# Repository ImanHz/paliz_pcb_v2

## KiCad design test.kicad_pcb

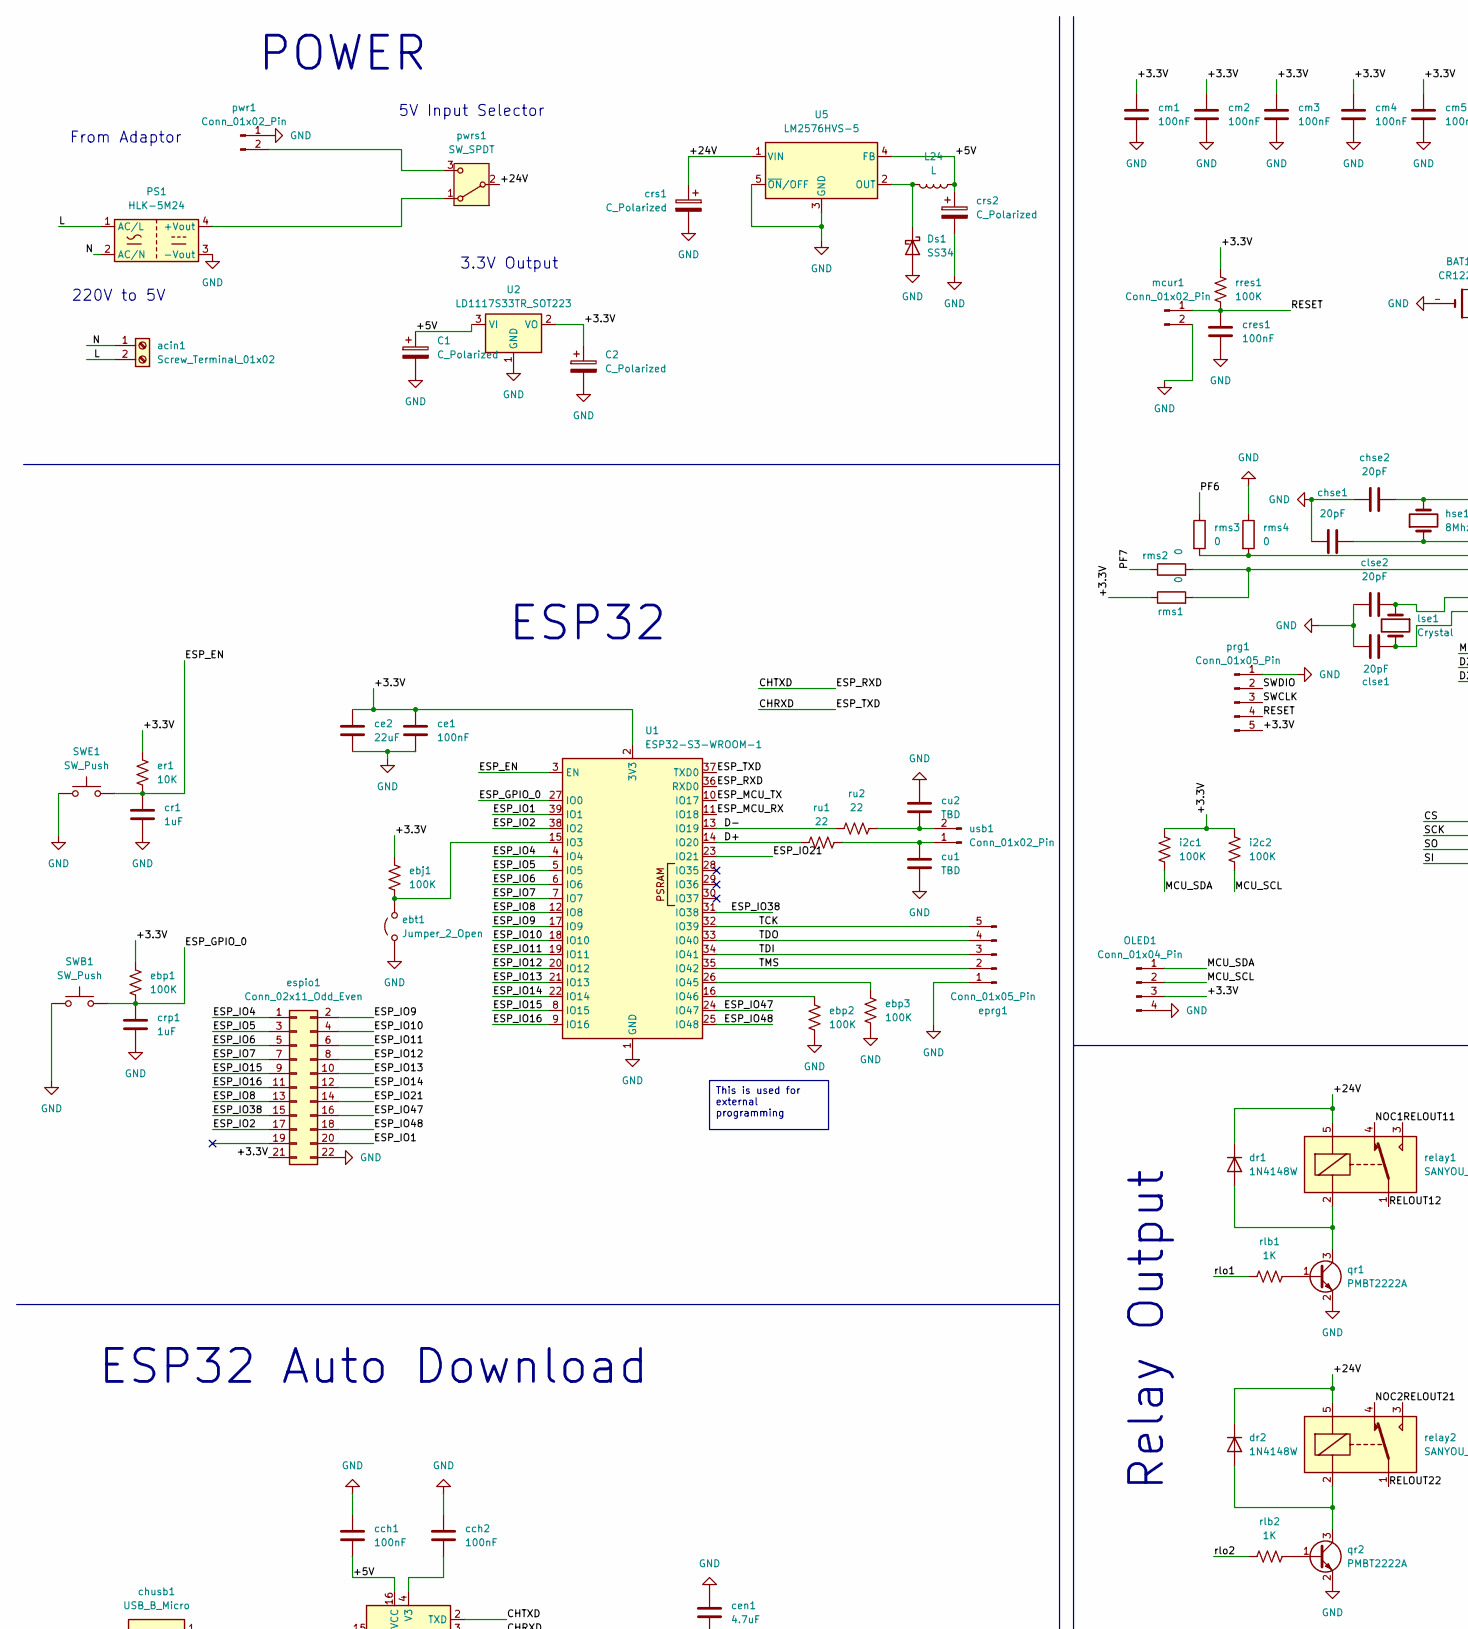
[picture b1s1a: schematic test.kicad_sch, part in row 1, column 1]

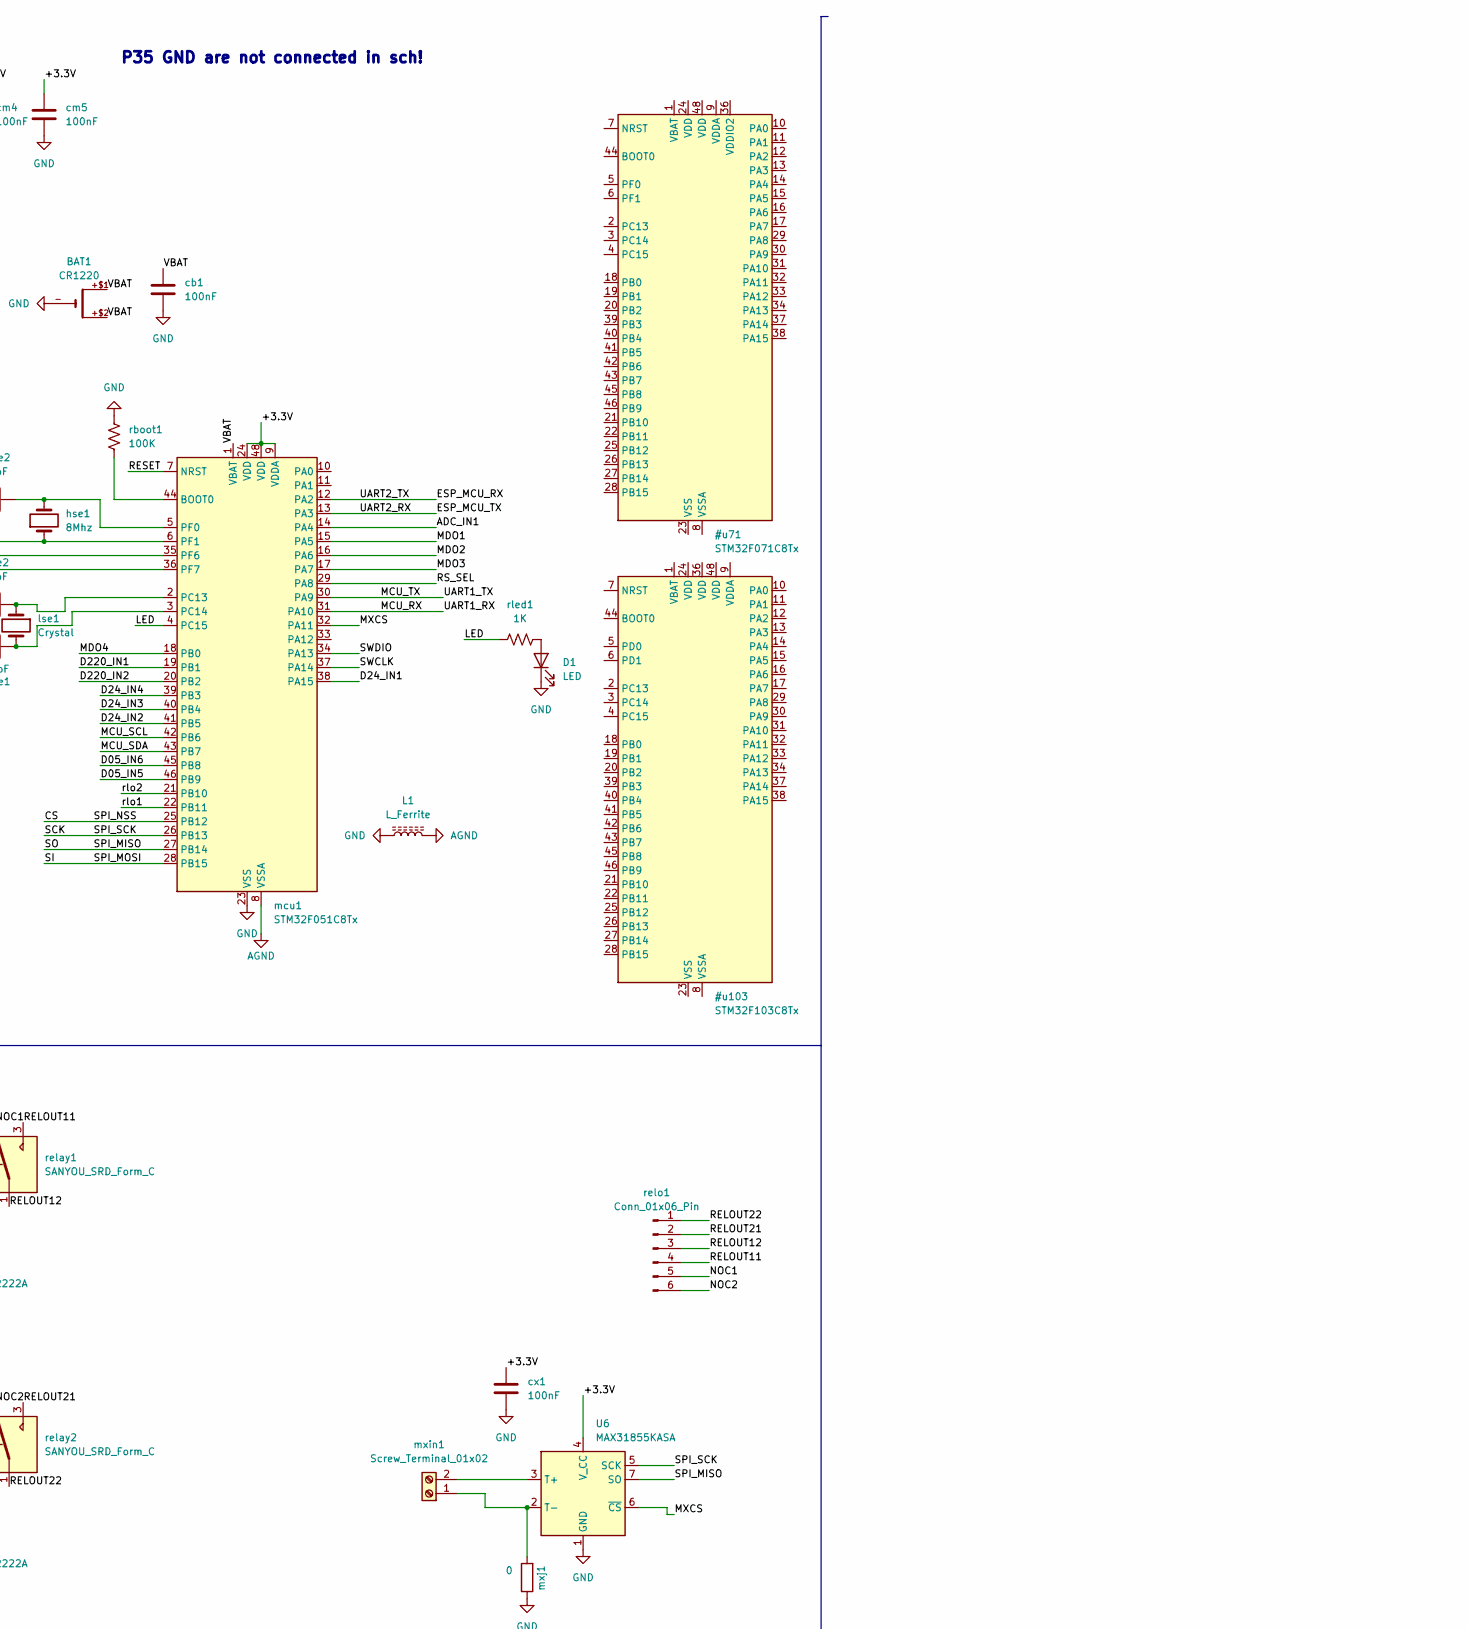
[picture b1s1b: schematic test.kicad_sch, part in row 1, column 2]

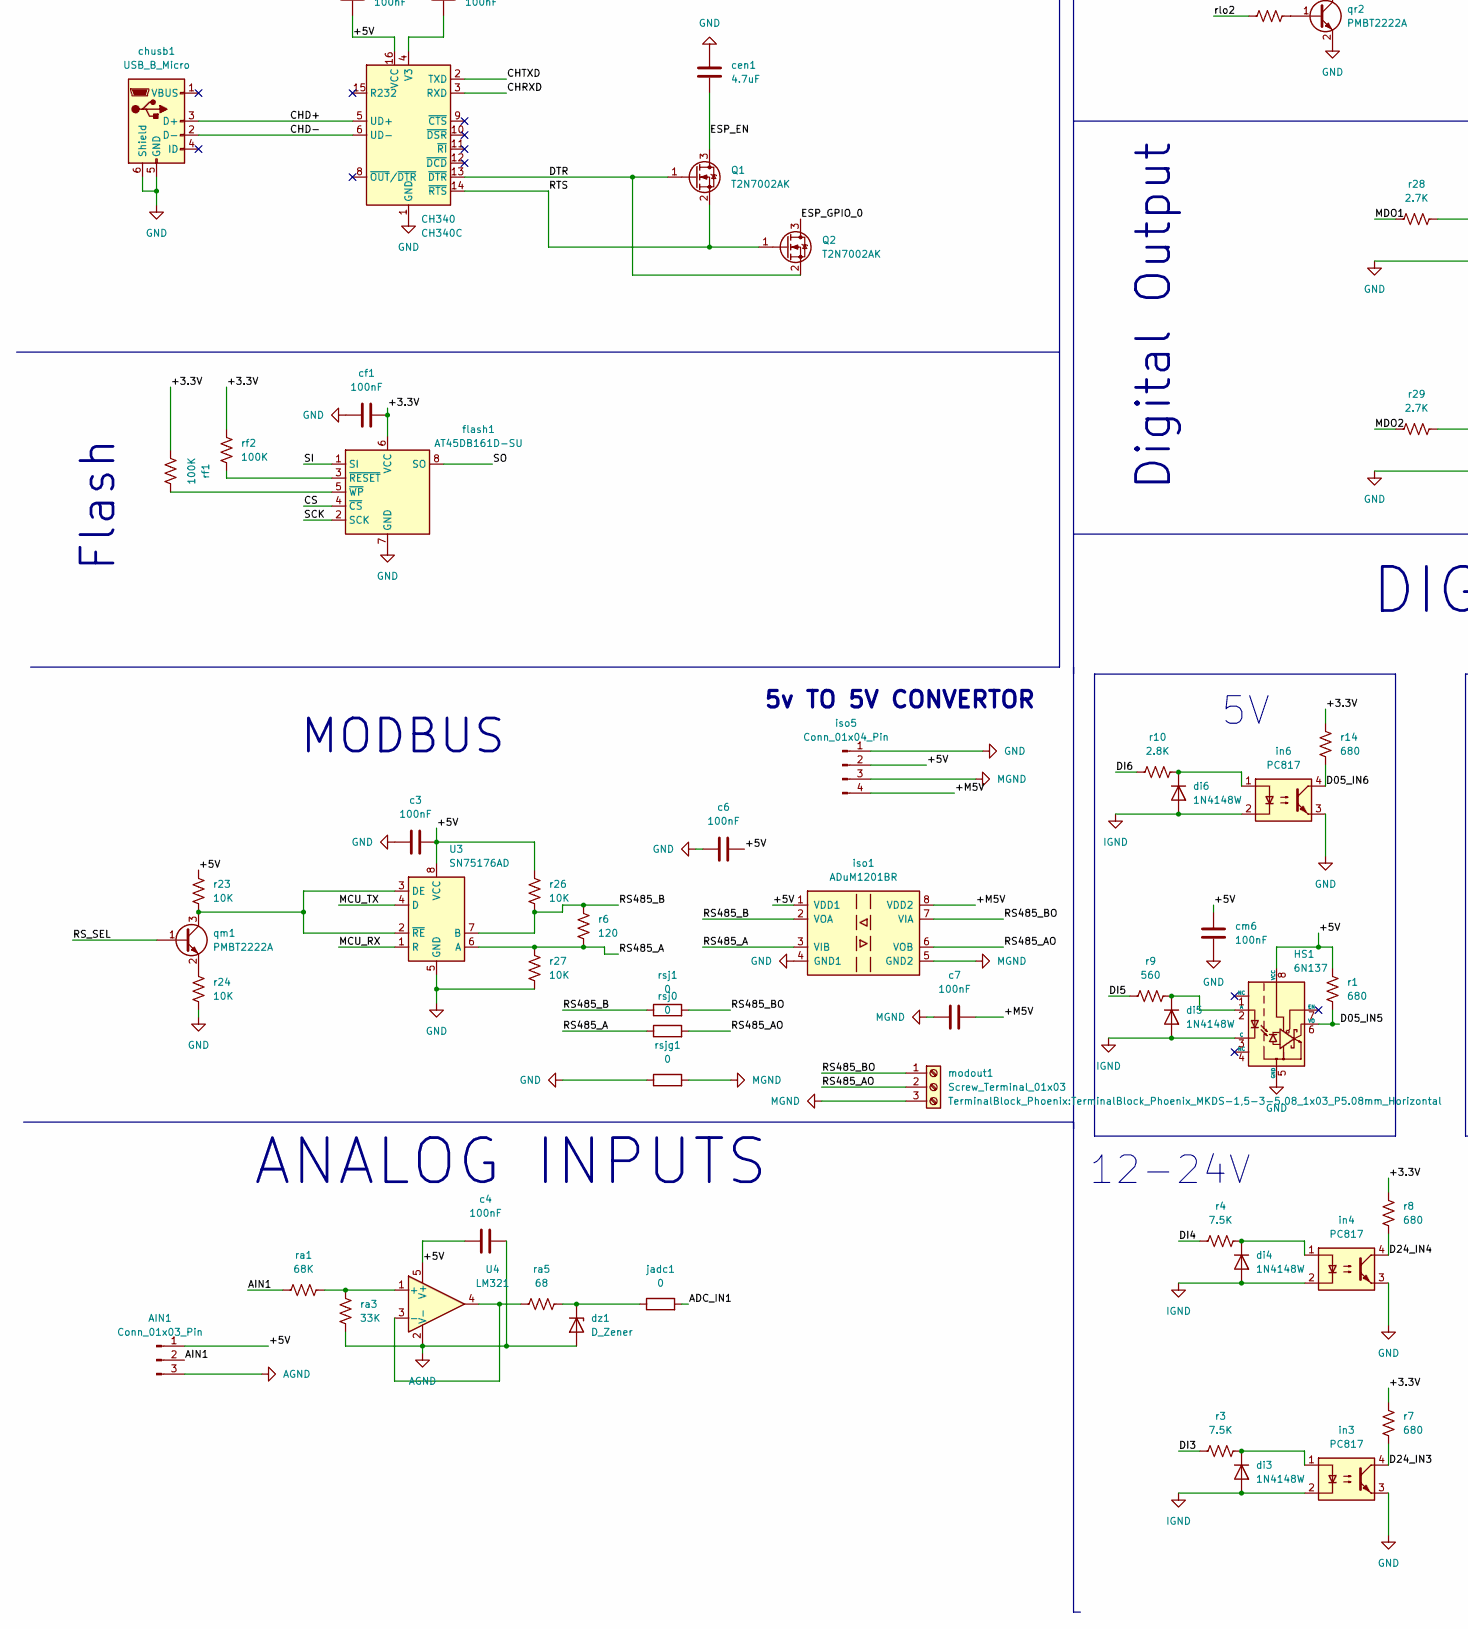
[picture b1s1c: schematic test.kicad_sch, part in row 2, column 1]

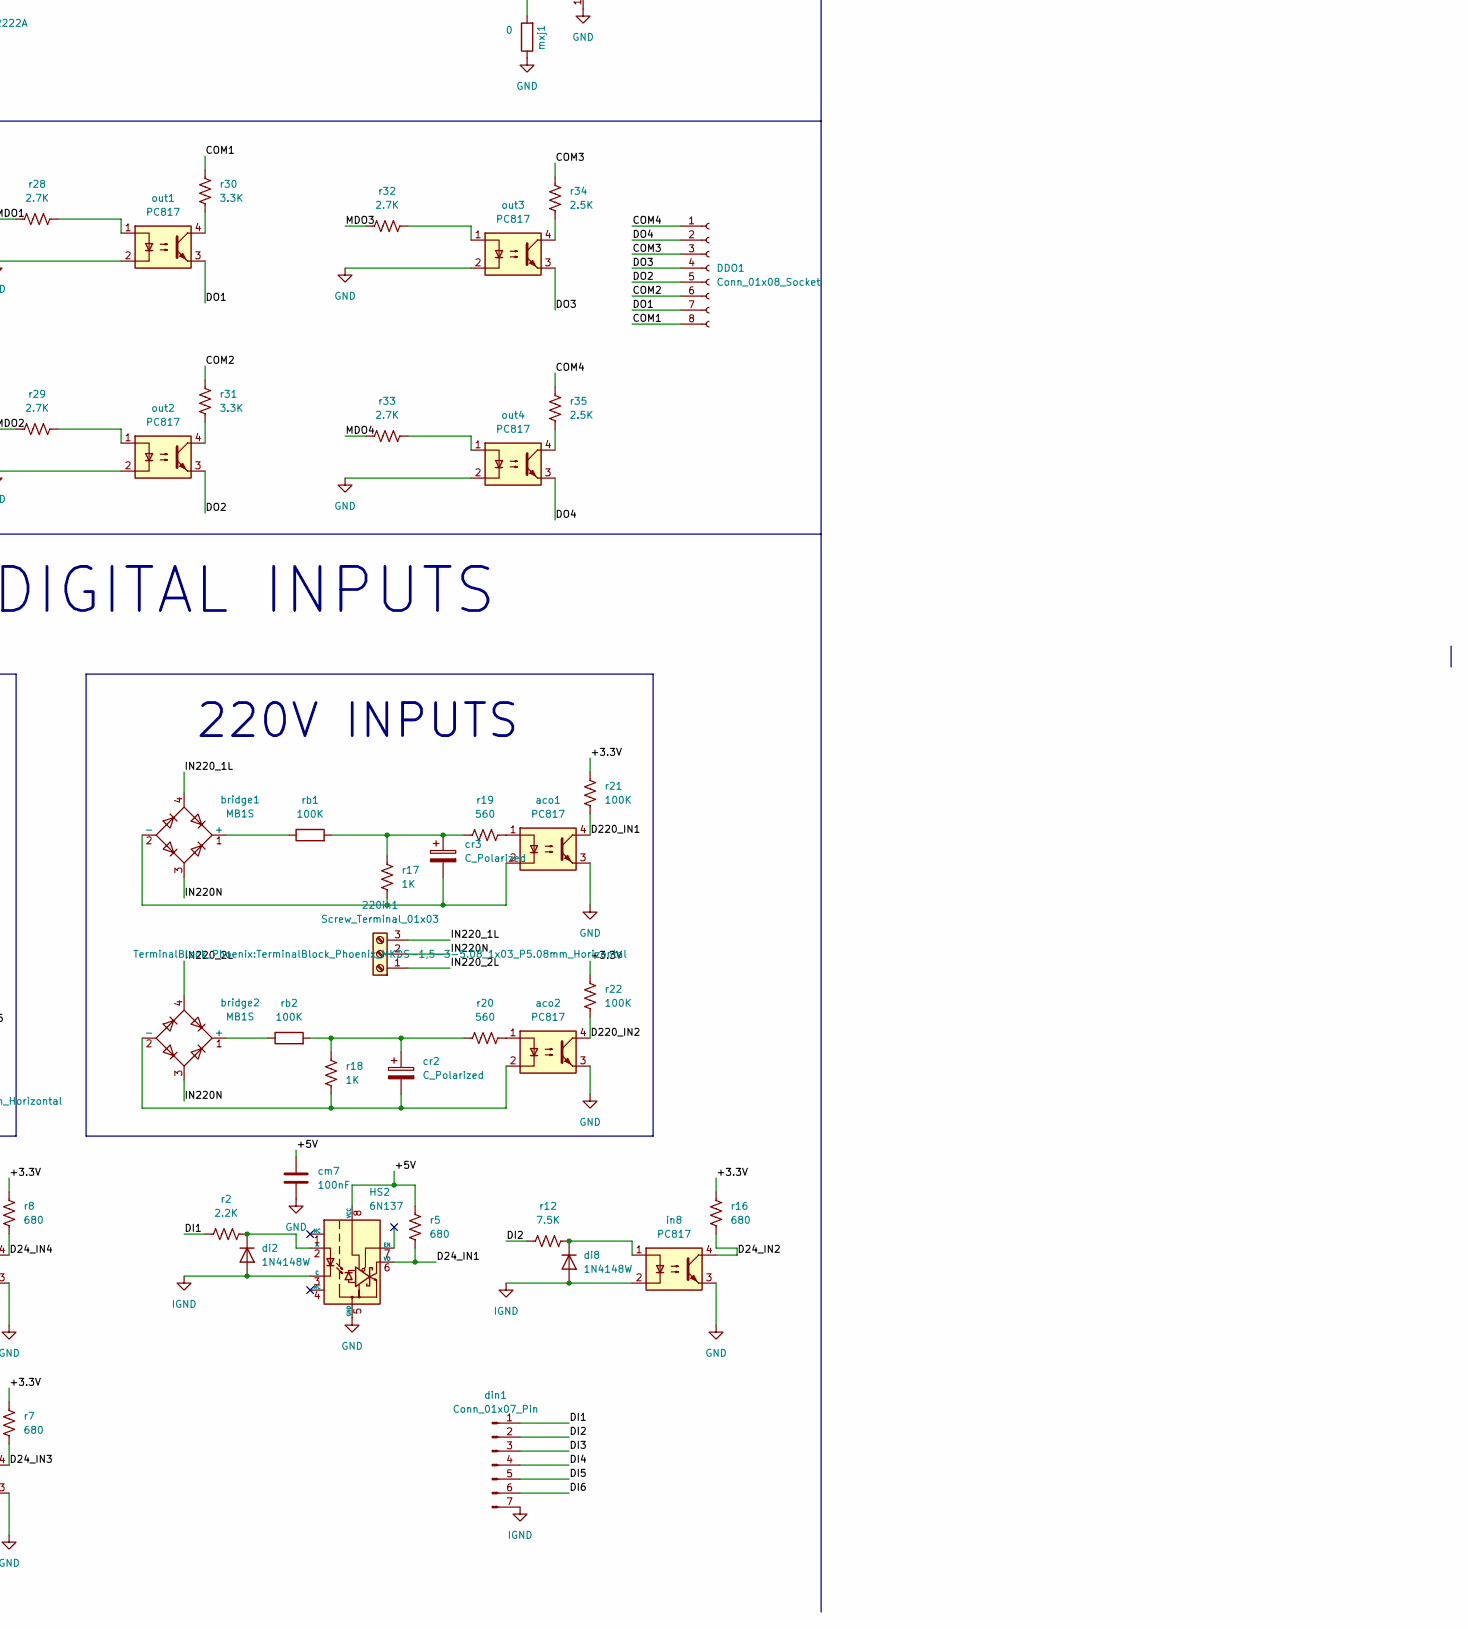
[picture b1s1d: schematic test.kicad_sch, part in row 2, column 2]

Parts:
220in1: Screw_Terminal_01x03; TerminalBlock_Phoenix_MKDS-1,5-3-5.08_1x03_P5.08mm_Horizont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
AIN1: Conn_01x03_Pin; Molex_KK-254_AE-6410-03A_1x03_P2.54mm_Vertical
BAT1: CR1220; CR1220-SMD
C1, C2: C_Polarized; CP_Radial_D4.0mm_P1.50mm
CH340: CH340C; SOIC-16_3.9x9.9mm_P1.27mm
D1: LED; LED_0805_2012Metric_Pad1.15x1.40mm_HandSolder
DDO1: Conn_01x08_Socket; Molex_KK-254_AE-6410-08A_1x08_P2.54mm_Vertical
Ds1: SS34; D_SMA
HS1, HS2: 6N137; DIP-8_W7.62mm
L1: L_Ferrite; L_0805_2012Metric_Pad1.05x1.20mm_HandSolder
L24: L; L_Radial_D9.5mm_P5.00mm_Fastron_07HVP
OLED1: Conn_01x04_Pin; Molex_KK-254_AE-6410-04A_1x04_P2.54mm_Vertical
PS1: HLK-5M24; Converter_ACDC_Hi-Link_HLK-5Mxx
Q1, Q2: T2N7002AK; SOT-23
SWB1: SW_Push; SW_Push_1P1T_NO_6x6mm_H9.5mm
SWE1: SW_Push; SW_Push_1P1T_NO_6x6mm_H9.5mm
U1: ESP32-S3-WROOM-1
U2: LD1117S33TR_SOT223; SOT-223-3_TabPin2
U3: SN75176AD; SOIC-8_3.9x4.9mm_P1.27mm
U4: LM321; SOT-23-5
U5: LM2576HVS-5; TO-263-5_TabPin3
U6: MAX31855KASA; SOIC-8_3.9x4.9mm_P1.27mm
acin1: Screw_Terminal_01x02; TerminalBlock_Phoenix_MKDS-1,5-2-5.08_1x02_P5.08mm_Horizont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
aco1, aco2: PC817; DIP-4_W7.62mm_SMDSocket_SmallPads
bridge1, bridge2: MB1S; Diode_Bridge_OnSemi_SDIP-4L
c3, c4, c6, c7: 100nF; C_0805_2012Metric_Pad1.18x1.45mm_HandSolder
cb1: 100nF; C_0805_2012Metric_Pad1.18x1.45mm_HandSolder
cch1, cch2: 100nF; C_0805_2012Metric_Pad1.18x1.45mm_HandSolder
ce1: 100nF; C_0805_2012Metric_Pad1.18x1.45mm_HandSolder
ce2: 22uF; C_0805_2012Metric_Pad1.18x1.45mm_HandSolder
cen1: 4.7uF; C_0805_2012Metric_Pad1.18x1.45mm_HandSolder
cf1: 100nF; C_0805_2012Metric_Pad1.18x1.45mm_HandSolder
chse1, chse2: 20pF; C_0805_2012Metric_Pad1.18x1.45mm_HandSolder
chusb1: USB_B_Micro; USB_Mini-B_Lumberg_2486_01_Horizontal
clse1, clse2: 20pF; C_0805_2012Metric_Pad1.18x1.45mm_HandSolder
cm1, cm2, cm3, cm4, cm5, cm6, cm7: 100nF; C_0805_2012Metric_Pad1.18x1.45mm_HandSolder
cr1: 1uF; C_0805_2012Metric_Pad1.18x1.45mm_HandSolder
cr2, cr3: C_Polarized; CP_Radial_D10.0mm_P3.80mm
cres1: 100nF; C_0805_2012Metric_Pad1.18x1.45mm_HandSolder
crp1: 1uF; C_0805_2012Metric_Pad1.18x1.45mm_HandSolder
crs1, crs2: C_Polarized; CP_Radial_D10.0mm_P3.80mm
cu1, cu2: TBD; C_0805_2012Metric_Pad1.18x1.45mm_HandSolder
cx1: 100nF; C_0805_2012Metric_Pad1.18x1.45mm_HandSolder
di2, di3, di4, di5, di6, di8: 1N4148W; D_SOD-123
din1: Conn_01x07_Pin; Molex_KK-254_AE-6410-07A_1x07_P2.54mm_Vertical
dr1, dr2: 1N4148W; D_SOD-123
dz1: D_Zener; D_MiniMELF_Handsoldering
ebj1: 100K; R_0805_2012Metric_Pad1.20x1.40mm_HandSolder
ebp1, ebp2, ebp3: 100K; R_0805_2012Metric_Pad1.20x1.40mm_HandSolder
ebt1: Jumper_2_Open; TestPoint_2Pads_Pitch2.54mm_Drill0.8mm
eprg1: Conn_01x05_Pin; Molex_KK-254_AE-6410-05A_1x05_P2.54mm_Vertical
er1: 10K; R_0805_2012Metric_Pad1.20x1.40mm_HandSolder
espio1: Conn_02x11_Odd_Even; PinHeader_2x11_P2.00mm_Vertical
flash1: AT45DB161D-SU; SOIC-8_5.275x5.275mm_P1.27mm
hse1: 8Mhz; Crystal_SMD_HC49-SD
i2c1, i2c2: 100K; R_0805_2012Metric_Pad1.20x1.40mm_HandSolder
in3, in4, in6, in8: PC817; DIP-4_W7.62mm_SMDSocket_SmallPads
iso1: ADuM1201BR; SOIC-8_3.9x4.9mm_P1.27mm
iso5: Conn_01x04_Pin; Molex_KK-254_AE-6410-04A_1x04_P2.54mm_Vertical
jadc1: 0; R_0805_2012Metric_Pad1.20x1.40mm_HandSolder
lse1: Crystal; Crystal_AT310_D3.0mm_L10.0mm_Horizontal
mcu1: STM32F051C8Tx; LQFP-48_7x7mm_P0.5mm
mcur1: Conn_01x02_Pin; PinHeader_1x02_P2.54mm_Vertical
modout1: Screw_Terminal_01x03; TerminalBlock_Phoenix_MKDS-1,5-3-5.08_1x03_P5.08mm_Horizont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
mxin1: Screw_Terminal_01x02; TerminalBlock_Phoenix_MKDS-1,5-2-5.08_1x02_P5.08mm_Horizont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
mxj1: 0; R_0805_2012Metric_Pad1.20x1.40mm_HandSolder
out1, out2, out3, out4: PC817; DIP-4_W7.62mm_SMDSocket_SmallPads
prg1: Conn_01x05_Pin; Molex_KK-254_AE-6410-05A_1x05_P2.54mm_Vertical
pwr1: Conn_01x02_Pin; Molex_KK-254_AE-6410-02A_1x02_P2.54mm_Vertical
pwrs1: SW_SPDT; PinHeader_1x03_P2.54mm_Vertical
qm1: PMBT2222A; SOT-23
qr1, qr2: PMBT2222A; SOT-23
r1, r5, r7, r8, r14, r16: 680; R_0805_2012Metric_Pad1.20x1.40mm_HandSolder
r2: 2.2K; R_1206_3216Metric_Pad1.30x1.75mm_HandSolder
r3, r4, r12: 7.5K; R_1206_3216Metric_Pad1.30x1.75mm_HandSolder
r6: 120; R_0805_2012Metric_Pad1.20x1.40mm_HandSolder
r9: 560; R_1206_3216Metric_Pad1.30x1.75mm_HandSolder
r10: 2.8K; R_1206_3216Metric_Pad1.30x1.75mm_HandSolder
r17, r18: 1K; R_0805_2012Metric_Pad1.20x1.40mm_HandSolder
r19, r20: 560; R_0805_2012Metric_Pad1.20x1.40mm_HandSolder
r21, r22: 100K; R_0805_2012Metric_Pad1.20x1.40mm_HandSolder
r23, r24, r26, r27: 10K; R_0805_2012Metric_Pad1.20x1.40mm_HandSolder
r28, r29, r32, r33: 2.7K; R_1206_3216Metric_Pad1.30x1.75mm_HandSolder
r30, r31: 3.3K; R_0805_2012Metric_Pad1.20x1.40mm_HandSolder
r34, r35: 2.5K; R_0805_2012Metric_Pad1.20x1.40mm_HandSolder
ra1: 68K; R_0805_2012Metric_Pad1.20x1.40mm_HandSolder
ra3: 33K; R_0805_2012Metric_Pad1.20x1.40mm_HandSolder
ra5: 68; R_0805_2012Metric_Pad1.20x1.40mm_HandSolder
rb1, rb2: 100K; R_Axial_DIN0414_L11.9mm_D4.5mm_P20.32mm_Horizontal
rboot1: 100K; R_0805_2012Metric_Pad1.20x1.40mm_HandSolder
relay1, relay2: SANYOU_SRD_Form_C; Relay_SPDT_SANYOU_SRD_Series_Form_C
relo1: Conn_01x06_Pin; Molex_KK-254_AE-6410-06A_1x06_P2.54mm_Vertical
rf1, rf2: 100K; R_0805_2012Metric_Pad1.20x1.40mm_HandSolder
rlb1, rlb2: 1K; R_0805_2012Metric_Pad1.20x1.40mm_HandSolder
rled1: 1K; R_0805_2012Metric_Pad1.20x1.40mm_HandSolder
rms1, rms2, rms3, rms4: 0; R_0805_2012Metric_Pad1.20x1.40mm_HandSolder
rres1: 100K; R_0805_2012Metric_Pad1.20x1.40mm_HandSolder
rsj0, rsj1: 0; R_0805_2012Metric_Pad1.20x1.40mm_HandSolder
rsjg1: 0; R_0805_2012Metric_Pad1.20x1.40mm_HandSolder
ru1, ru2: 22; R_0805_2012Metric_Pad1.20x1.40mm_HandSolder
usb1: Conn_01x02_Pin; Molex_KK-254_AE-6410-02A_1x02_P2.54mm_Vertical

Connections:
/+3.3V: C2.1, OLED1.3, U1.2 (3V3), U2.2 (VO), U6.4 (V_CC), ce1.1, ce2.1, cf1.2, cm1.1, cm2.1, cm3.1, cm4.1, cm5.1, cx1.1, ebj1.1, ebp1.1, er1.1, espio1.21, flash1.6 (VCC), i2c1.1, i2c2.1, mcu1.9 (VDDA), mcu1.24 (VDD), mcu1.48 (VDD), prg1.5, r7.2, r8.2, r14.2, r16.2, r21.2, r22.2, rf1.1, rf2.1, rms1.1, rres1.1; also elsewhere on the board
/+5V: AIN1.1, C1.1, CH340.16 (VCC), HS1.8 (VCC), HS2.8 (VCC), L24.1, U2.3 (VI), U3.8 (VCC), U4.5 (V+), U5.4 (FB), c3.2, c4.1, c6.2, cch1.1, cm6.1, cm7.1, crs2.1, iso1.1 (VDD1), iso5.2, r1.2, r5.2, r23.2, r26.2
/+24V: U5.1 (VIN), crs1.1, dr1.1 (K), dr2.1 (K), pwrs1.2 (B), relay1.5, relay2.5; also elsewhere on the board
/+M5V: c7.2, iso1.8 (VDD2), iso5.4
/ADC_IN1: jadc1.2, mcu1.14 (PA4)
/AIN1: AIN1.2, ra1.1
/CHD+: CH340.5 (UD+), chusb1.3 (D+); also elsewhere on the board
/CHD-: CH340.6 (UD-), chusb1.2 (D-); also elsewhere on the board
/CHRXD: CH340.3 (RXD), U1.37 (TXD0)
/CHTXD: CH340.2 (TXD), U1.36 (RXD0)
/COM1: DDO1.8, r30.2
/COM2: DDO1.6, r31.2
/COM3: DDO1.3, r34.2
/COM4: DDO1.1, r35.2
/CS: flash1.4 (~CS), mcu1.25 (PB12)
/D05_IN5: HS1.6 (VO), mcu1.46 (PB9), r1.1
/D05_IN6: in6.4, mcu1.45 (PB8), r14.1
/D24_IN1: HS2.6 (VO), mcu1.38 (PA15), r5.1
/D24_IN2: in8.4, mcu1.41 (PB5), r16.1
/D24_IN3: in3.4, mcu1.40 (PB4), r7.1
/D24_IN4: in4.4, mcu1.39 (PB3), r8.1
/D220_IN1: aco1.4, mcu1.19 (PB1), r21.1
/D220_IN2: aco2.4, mcu1.20 (PB2), r22.1
/D+: U1.14 (IO20), ru1.1
/D-: U1.13 (IO19), ru2.1
/DI1: din1.1, r2.1; also elsewhere on the board
/DI2: din1.2, r12.1; also elsewhere on the board
/DI3: din1.3, r3.1; also elsewhere on the board
/DI4: din1.4, r4.1; also elsewhere on the board
/DI5: din1.5, r9.1; also elsewhere on the board
/DI6: din1.6, r10.1; also elsewhere on the board
/DO1: DDO1.7, out1.3
/DO2: DDO1.5, out2.3
/DO3: DDO1.4, out3.3
/DO4: DDO1.2, out4.3
/DTR: CH340.13 (~DTR), Q1.1 (G), Q2.2 (S)
/ESP_EN: Q1.3 (D), SWE1.2, U1.3 (EN), cen1.2, cr1.1, er1.2
/ESP_GPIO_0: Q2.3 (D), SWB1.2, U1.27 (IO0), crp1.1, ebp1.2
/ESP_IO1: U1.39 (IO1), espio1.20
/ESP_IO2: U1.38 (IO2), espio1.17
/ESP_IO4: U1.4 (IO4), espio1.1
/ESP_IO5: U1.5 (IO5), espio1.3
/ESP_IO6: U1.6 (IO6), espio1.5
/ESP_IO7: U1.7 (IO7), espio1.7
/ESP_IO8: U1.12 (IO8), espio1.13
/ESP_IO9: U1.17 (IO9), espio1.2
/ESP_IO10: U1.18 (IO10), espio1.4
/ESP_IO11: U1.19 (IO11), espio1.6
/ESP_IO12: U1.20 (IO12), espio1.8
/ESP_IO13: U1.21 (IO13), espio1.10
/ESP_IO14: U1.22 (IO14), espio1.12
/ESP_IO15: U1.8 (IO15), espio1.9
/ESP_IO16: U1.9 (IO16), espio1.11
/ESP_IO21: U1.23 (IO21), espio1.14
/ESP_IO38: U1.31 (IO38), espio1.15
/ESP_IO47: U1.24 (IO47), espio1.16
/ESP_IO48: U1.25 (IO48), espio1.18
/ESP_MCU_RX: U1.11 (IO18), mcu1.12 (PA2)
/ESP_MCU_TX: U1.10 (IO17), mcu1.13 (PA3)
/IN220N: 220in1.2, bridge1.3, bridge2.3
/IN220_1L: 220in1.3, bridge1.4
/IN220_2L: 220in1.1, bridge2.4
/L: PS1.1 (AC/L), acin1.2
/LED: mcu1.4 (PC15), rled1.1
/MCU_RX: U3.1 (R), mcu1.31 (PA10)
/MCU_SCL: OLED1.2, i2c2.2, mcu1.42 (PB6)
/MCU_SDA: OLED1.1, i2c1.2, mcu1.43 (PB7)
/MCU_TX: U3.4 (D), mcu1.30 (PA9)
/MDO1: mcu1.15 (PA5), r28.1
/MDO2: mcu1.16 (PA6), r29.1
/MDO3: mcu1.17 (PA7), r32.1
/MDO4: mcu1.18 (PB0), r33.1
/MXCS: U6.6 (~CS), mcu1.32 (PA11)
/N: PS1.2 (AC/N), acin1.1
/NOC1: relay1.4, relo1.5; also elsewhere on the board
/NOC2: relay2.4, relo1.6; also elsewhere on the board
/PF6: rms3.1
/PF7: rms2.1
/RELOUT11: relay1.3, relo1.4; also elsewhere on the board
/RELOUT12: relay1.1, relo1.3; also elsewhere on the board
/RELOUT21: relay2.3, relo1.2; also elsewhere on the board
/RELOUT22: relay2.1, relo1.1; also elsewhere on the board
/RESET: cres1.1, mcu1.7 (NRST), mcur1.1, prg1.4, rres1.2; also elsewhere on the board
/RS485_A: U3.6 (A), iso1.3 (VIB), r6.2, r27.2, rsj0.1
/RS485_AO: iso1.6 (VOB), modout1.2, rsj0.2; also elsewhere on the board
/RS485_B: U3.7 (B), iso1.2 (VOA), r6.1, r26.1, rsj1.1
/RS485_BO: iso1.7 (VIA), modout1.1, rsj1.2; also elsewhere on the board
/RS_SEL: mcu1.29 (PA8), qm1.1 (B)
/RTS: CH340.14 (~RTS), Q1.2 (S), Q2.1 (G)
/SCK: U6.5 (SCK), flash1.2 (SCK), mcu1.26 (PB13)
/SI: flash1.1 (SI), mcu1.28 (PB15)
/SO: U6.7 (SO), flash1.8 (SO), mcu1.27 (PB14)
/SWCLK: mcu1.37 (PA14), prg1.3; also elsewhere on the board
/SWDIO: mcu1.34 (PA13), prg1.2; also elsewhere on the board
/TCK: U1.32 (IO39), eprg1.5
/TDI: U1.34 (IO41), eprg1.3
/TDO: U1.33 (IO40), eprg1.4
/TMS: U1.35 (IO42), eprg1.2
/VBAT: BAT1.+$1, BAT1.+$2, cb1.1, mcu1.1 (VBAT)
/rlo1: mcu1.22 (PB11), rlb1.1
/rlo2: mcu1.21 (PB10), rlb2.1
AGND: AIN1.3, L1.2, U4.2 (V-), c4.2, dz1.2 (A), mcu1.8 (VSSA), ra3.1
GND: BAT1.-, C1.2, C2.2, CH340.1 (GND), D1.1 (K), Ds1.2 (A), HS1.5 (GND), HS2.5 (GND), L1.1, OLED1.4, PS1.3 (-Vout), SWB1.1, SWE1.1, U1.1 (GND), U1.40 (GND), U1.41 (GND), U2.1 (GND), U3.5 (GND), U5.3 (GND), U5.5 (~ON/OFF), U6.1 (GND), aco1.3, aco2.3, c3.1, c6.1, cb1.2, cch1.2, cch2.1, ce1.2, ce2.2, cen1.1, cf1.1, chse1.1, chse2.1, chusb1.5 (GND), chusb1.6 (Shield), clse1.1, clse2.1, cm1.2, cm2.2, cm3.2, cm4.2, cm5.2, cm6.2, cm7.2, cr1.2, cres1.2, crp1.2, crs1.2, crs2.2, cu1.2, cu2.1, cx1.2, ebp2.2, ebp3.2, ebt1.1 (A), eprg1.1, espio1.22, flash1.7 (GND), in3.3, in4.3, in6.3, in8.3, iso1.4 (GND1), iso5.1, mcu1.23 (VSS), mcu1.47 (VSS), mcur1.2, mxj1.1, out1.2, out2.2, out3.2, out4.2, prg1.1, pwr1.1, qr1.2 (E), qr2.2 (E), r24.2, r27.1, rboot1.1, rms4.1, rsjg1.1; also elsewhere on the board
IGND: HS1.3 (C), HS2.3 (C), di2.2 (A), di3.2 (A), di4.2 (A), di5.2 (A), di6.2 (A), di8.2 (A), din1.7, in3.2, in4.2, in6.2, in8.2; also elsewhere on the board
MGND: c7.1, iso1.5 (GND2), iso5.3, modout1.3, rsjg1.2; also elsewhere on the board
unnamed: CH340.4 (V3), cch2.2
unnamed: D1.2 (A), rled1.2
unnamed: Ds1.1 (K), L24.2, U5.2 (OUT)
unnamed: HS1.2 (A), di5.1 (K), r9.2
unnamed: HS2.2 (A), di2.1 (K), r2.2
unnamed 110: PS1.4 (+Vout), pwrs1.1 (A); also elsewhere on the board
unnamed 111: U1.15 (IO3), ebj1.2, ebt1.2 (B); also elsewhere on the board
unnamed: U1.26 (IO45), ebp3.1
unnamed: U1.16 (IO46), ebp2.1
unnamed: U3.2 (~RE), U3.3 (DE), qm1.3 (C), r23.1
unnamed: U4.1 (+), ra1.2, ra3.2
unnamed: U4.3 (-), U4.4, ra5.1
unnamed 117: U6.3 (T+), mxin1.2; also elsewhere on the board
unnamed 118: U6.2 (T-), mxin1.1, mxj1.2; also elsewhere on the board
unnamed: aco1.1, r19.1
unnamed: aco2.1, r20.1
unnamed: bridge1.1 (+), rb1.1
unnamed: aco1.2, bridge1.2 (-), cr3.2, r17.1
unnamed: bridge2.1 (+), rb2.1
unnamed: aco2.2, bridge2.2 (-), cr2.2, r18.1
unnamed: cr2.1, r18.2, r20.2, rb2.2
unnamed: cr3.1, r17.2, r19.2, rb1.2
unnamed: di3.1 (K), in3.1, r3.2
unnamed: di4.1 (K), in4.1, r4.2
unnamed: di6.1 (K), in6.1, r10.2
unnamed: di8.1 (K), in8.1, r12.2
unnamed: dr1.2 (A), qr1.3 (C), relay1.2
unnamed: dr2.2 (A), qr2.3 (C), relay2.2
unnamed: dz1.1 (K), jadc1.1, ra5.2
unnamed: flash1.3 (~RESET), rf2.2
unnamed: flash1.5 (~WP), rf1.2
unnamed: mcu1.44 (BOOT0), rboot1.2
unnamed: clse2.2, lse1.1, mcu1.2 (PC13)
unnamed: clse1.2, lse1.2, mcu1.3 (PC14)
unnamed: chse2.2, hse1.2, mcu1.5 (PF0)
unnamed: chse1.2, hse1.1, mcu1.6 (PF1)
unnamed: mcu1.35 (PF6), rms3.2, rms4.2
unnamed: mcu1.36 (PF7), rms1.2, rms2.2
unnamed: out1.1, r28.2
unnamed: out1.4, r30.1
unnamed: out2.1, r29.2
unnamed: out2.4, r31.1
unnamed: out3.1, r32.2
unnamed: out3.4, r34.1
unnamed: out4.1, r33.2
unnamed: out4.4, r35.1
unnamed: pwr1.2, pwrs1.3 (C)
unnamed: qm1.2 (E), r24.1
unnamed: qr1.1 (B), rlb1.2
unnamed: qr2.1 (B), rlb2.2
unnamed: cu1.1, ru1.2, usb1.1
unnamed: cu2.2, ru2.2, usb1.2

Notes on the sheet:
This is used for external programming
ESP32
Digital Output
5V Input Selector
ESP32 Auto Download
From Adaptor
MODBUS
POWER
3.3V Output
P35 GND are not connected in sch!
12-24V
220V to 5V
DIGITAL INPUTS
5v TO 5V CONVERTOR
220V INPUTS
Flash
ANALOG INPUTS
Relay Output

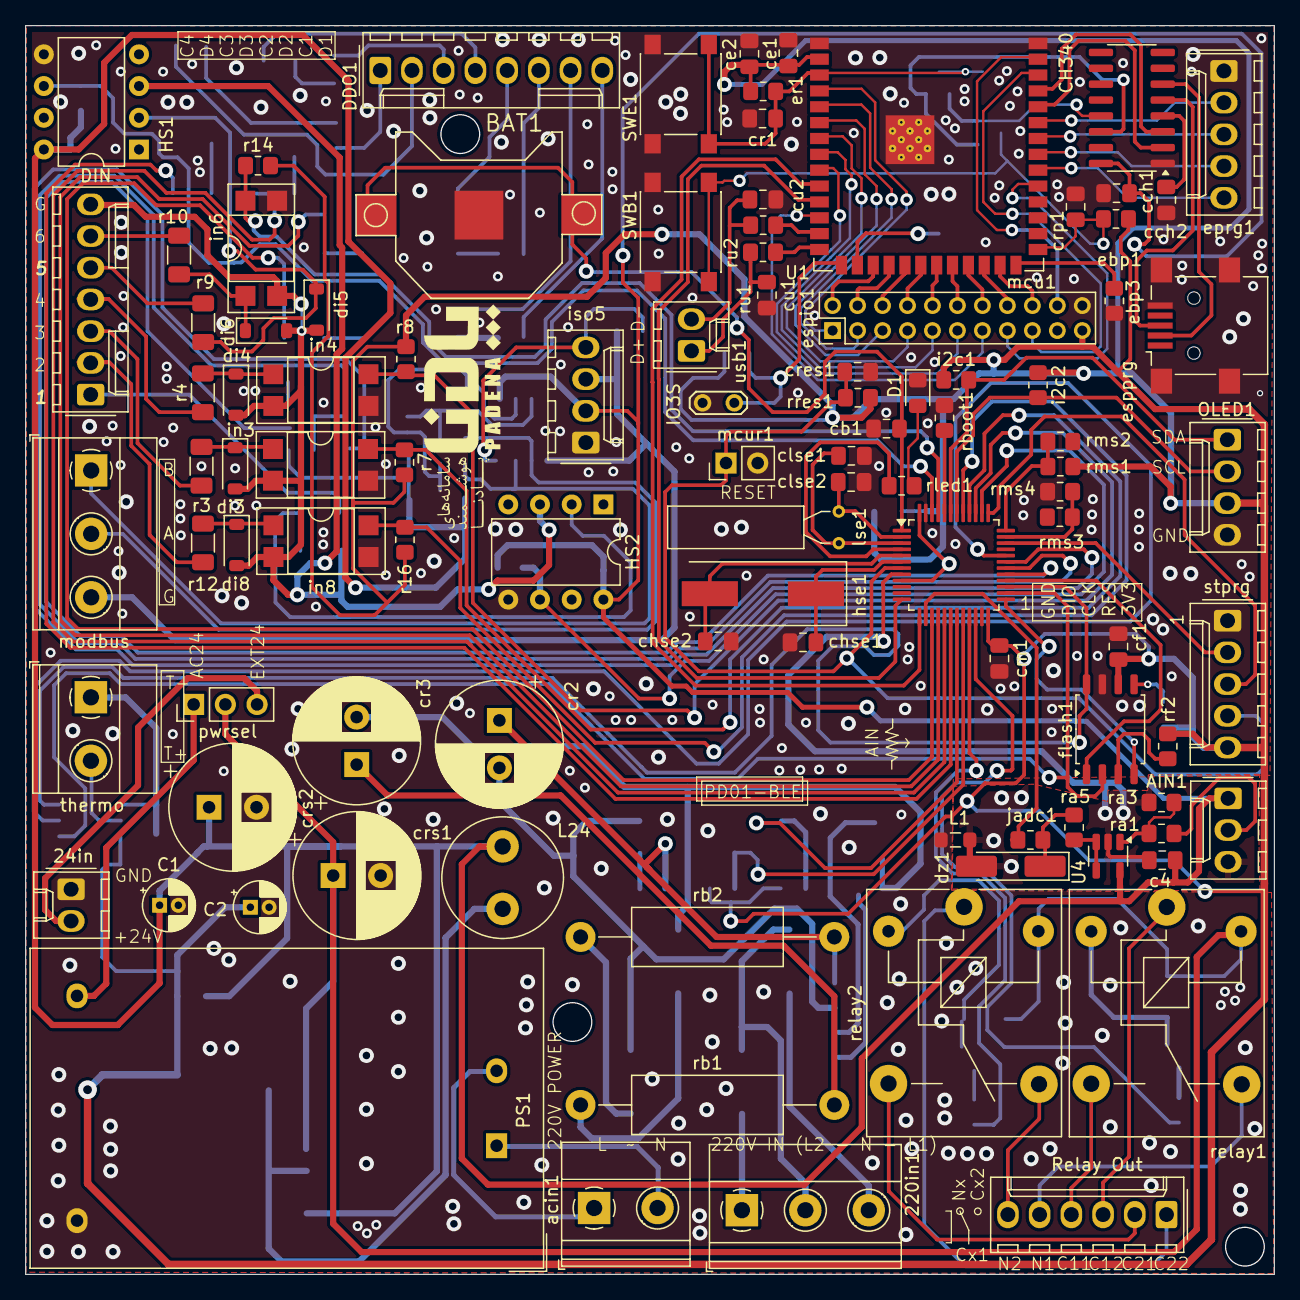
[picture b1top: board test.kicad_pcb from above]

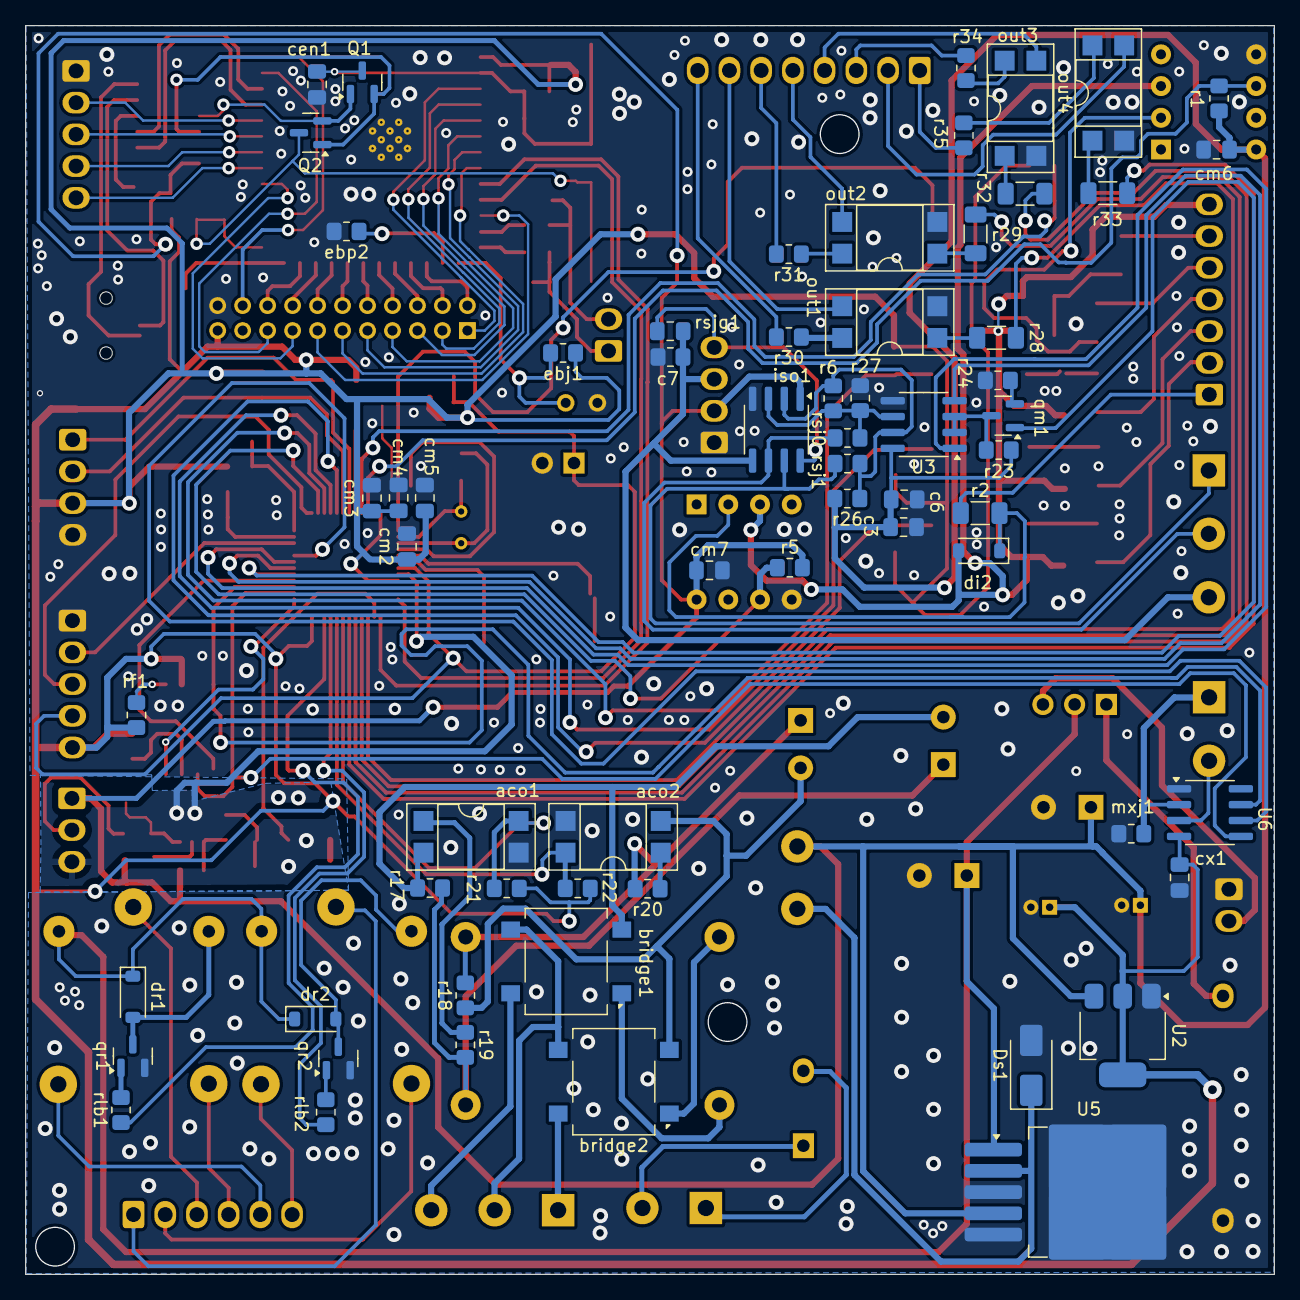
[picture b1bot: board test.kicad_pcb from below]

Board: 2 copper layers, 100.0 x 100.0 mm, 164 parts (64 on the bottom side), 155 nets.

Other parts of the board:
24in: Conn_01x02_Pin; Molex_KK-254_AE-6410-02A_1x02_P2.54mm_Vertical
DIN: Conn_01x07_Pin; Molex_KK-254_AE-6410-07A_1x07_P2.54mm_Vertical
IO3S: Jumper_2_Open; TestPoint_2Pads_Pitch2.54mm_Drill0.8mm
Relay Out: Conn_01x06_Pin; Molex_KK-254_AE-6410-06A_1x06_P2.54mm_Vertical
espprg: USB_B_Micro; USB_Mini-B_Lumberg_2486_01_Horizontal
modbus: Screw_Terminal_01x03; TerminalBlock_Phoenix_MKDS-1,5-3-5.08_1x03_P5.08mm_Horizont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
pwrsel: SW_SPDT; PinHeader_1x03_P2.54mm_Vertical
stprg: Conn_01x05_Pin; Molex_KK-254_AE-6410-05A_1x05_P2.54mm_Vertical
thermo: Screw_Terminal_01x02; TerminalBlock_Phoenix_MKDS-1,5-2-5.08_1x02_P5.08mm_Horizont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

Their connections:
/+3.3V: stprg.5; also elsewhere on the board
/+24V: pwrsel.2 (B); also elsewhere on the board
/CHD+: espprg.3 (D+); also elsewhere on the board
/CHD-: espprg.2 (D-); also elsewhere on the board
/DI1: DIN.1; also elsewhere on the board
/DI2: DIN.2; also elsewhere on the board
/DI3: DIN.3; also elsewhere on the board
/DI4: DIN.4; also elsewhere on the board
/DI5: DIN.5; also elsewhere on the board
/DI6: DIN.6; also elsewhere on the board
/NOC1: Relay Out.5; also elsewhere on the board
/NOC2: Relay Out.6; also elsewhere on the board
/RELOUT11: Relay Out.4; also elsewhere on the board
/RELOUT12: Relay Out.3; also elsewhere on the board
/RELOUT21: Relay Out.2; also elsewhere on the board
/RELOUT22: Relay Out.1; also elsewhere on the board
/RESET: stprg.4; also elsewhere on the board
/RS485_AO: modbus.2; also elsewhere on the board
/RS485_BO: modbus.1; also elsewhere on the board
/SWCLK: stprg.3; also elsewhere on the board
/SWDIO: stprg.2; also elsewhere on the board
GND: 24in.1, IO3S.1 (A), espprg.5 (GND), espprg.6 (Shield), stprg.1; also elsewhere on the board
IGND: DIN.7; also elsewhere on the board
MGND: modbus.3; also elsewhere on the board
unnamed 110: pwrsel.1 (A); also elsewhere on the board
unnamed 111: IO3S.2 (B); also elsewhere on the board
unnamed 117: thermo.2; also elsewhere on the board
unnamed 118: thermo.1; also elsewhere on the board
unnamed: 24in.2, pwrsel.3 (C)

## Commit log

2024-05-10 added relays and optos
2024-05-12 schematic almost complete
2024-05-15 schematic complete
2024-05-18 finished power and esp32 in pcb
2024-05-19 pcb complete; size is the problem
2024-05-19 part placement done, semi routed
2024-05-19 final placement-no route
2024-05-20 except DI1-4 all other logics are ok
2024-05-21 all done except gnds and vccs
2024-05-22 all done but gnd
2024-05-23 final version. needs cleanup and marckage
2024-05-24 polygon and solder mask complete. DRC complete
2024-05-24 first version to print
2024-05-24 new gerber files
2024-05-25 changed ESP32 fottprint
